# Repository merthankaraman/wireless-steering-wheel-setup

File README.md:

# wireless-steering-wheel-setup
 Wireless steering wheel simulation setup

For 3d model of this project you can check out my friend's page on grabcad: <br>
https://grabcad.com/library/wireless-communication-steering-wheel-project-pedal-part-trial-1

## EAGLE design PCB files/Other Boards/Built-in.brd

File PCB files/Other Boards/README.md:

# arduino-uno-nrf2401
 Arduino board with nrf2401 and screw terminal pinout
 
### Schematic Of the Shield
<br/><br/>

### Board Of the Shield
<br/><br/>

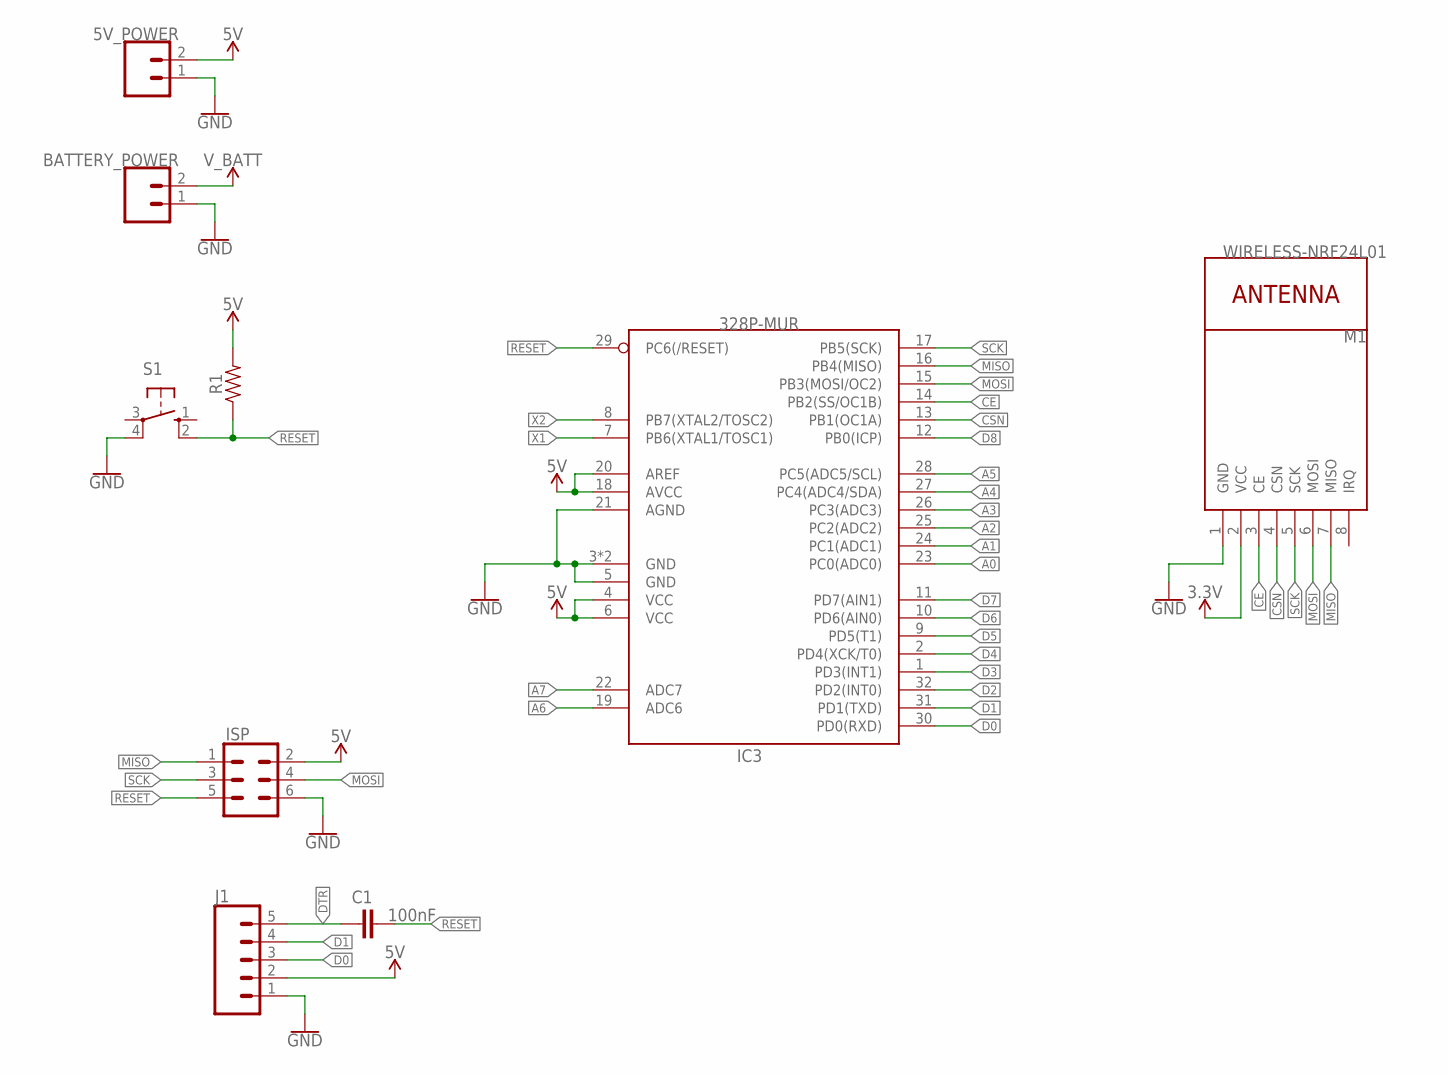
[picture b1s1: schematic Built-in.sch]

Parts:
5V_POWER: CONN_025MM; SCREWTERMINAL-5MM-2
BATTERY_POWER: CONN_025MM; SCREWTERMINAL-5MM-2
C1: 100nF; 0603
IC3: 328P-MUR; VQFN32
ISP: CONN_03X22X3_SILK_MALE_PTH; 2X3
J1: CONN_05; 1X05
M1: WIRELESS-NRF24L01
R1: 0402
S1: 40-XX; B3F-40XX

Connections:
3.3V: M1.2 (VCC)
5V: 5V_POWER.2, IC3.4 (VCC), IC3.6 (VCC), IC3.18 (AVCC), IC3.20 (AREF), ISP.2, J1.2, R1.2
A0: IC3.23 (PC0(ADC0))
A1: IC3.24 (PC1(ADC1))
A2: IC3.25 (PC2(ADC2))
A3: IC3.26 (PC3(ADC3))
A4: IC3.27 (PC4(ADC4/SDA))
A5: IC3.28 (PC5(ADC5/SCL))
A6: IC3.19 (ADC6)
A7: IC3.22 (ADC7)
CE: IC3.14 (PB2(SS/OC1B)), M1.3 (CE)
CSN: IC3.13 (PB1(OC1A)), M1.4 (CSN)
D0: IC3.30 (PD0(RXD)), J1.3
D1: IC3.31 (PD1(TXD)), J1.4
D2: IC3.32 (PD2(INT0))
D3: IC3.1 (PD3(INT1))
D4: IC3.2 (PD4(XCK/T0))
D5: IC3.9 (PD5(T1))
D6: IC3.10 (PD6(AIN0))
D7: IC3.11 (PD7(AIN1))
D8: IC3.12 (PB0(ICP))
DTR: C1.1, J1.5
GND: 5V_POWER.1, BATTERY_POWER.1, IC3.3 (GND), IC3.5 (GND), IC3.21 (AGND), IC3.33 (GND), ISP.6, J1.1, M1.1 (GND), S1.4 (P1)
MISO: IC3.16 (PB4(MISO)), ISP.1, M1.7 (MISO)
MOSI: IC3.15 (PB3(MOSI/OC2)), ISP.4, M1.6 (MOSI)
RESET: C1.2, IC3.29 (PC6(/RESET)), ISP.5, R1.1, S1.2 (S1)
SCK: IC3.17 (PB5(SCK)), ISP.3, M1.5 (SCK)
V_BATT: BATTERY_POWER.2
X1: IC3.7 (PB6(XTAL1/TOSC1))
X2: IC3.8 (PB7(XTAL2/TOSC2))

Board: 2 copper layers, 9 parts (0 on the bottom side), 11 nets, no tracks yet.

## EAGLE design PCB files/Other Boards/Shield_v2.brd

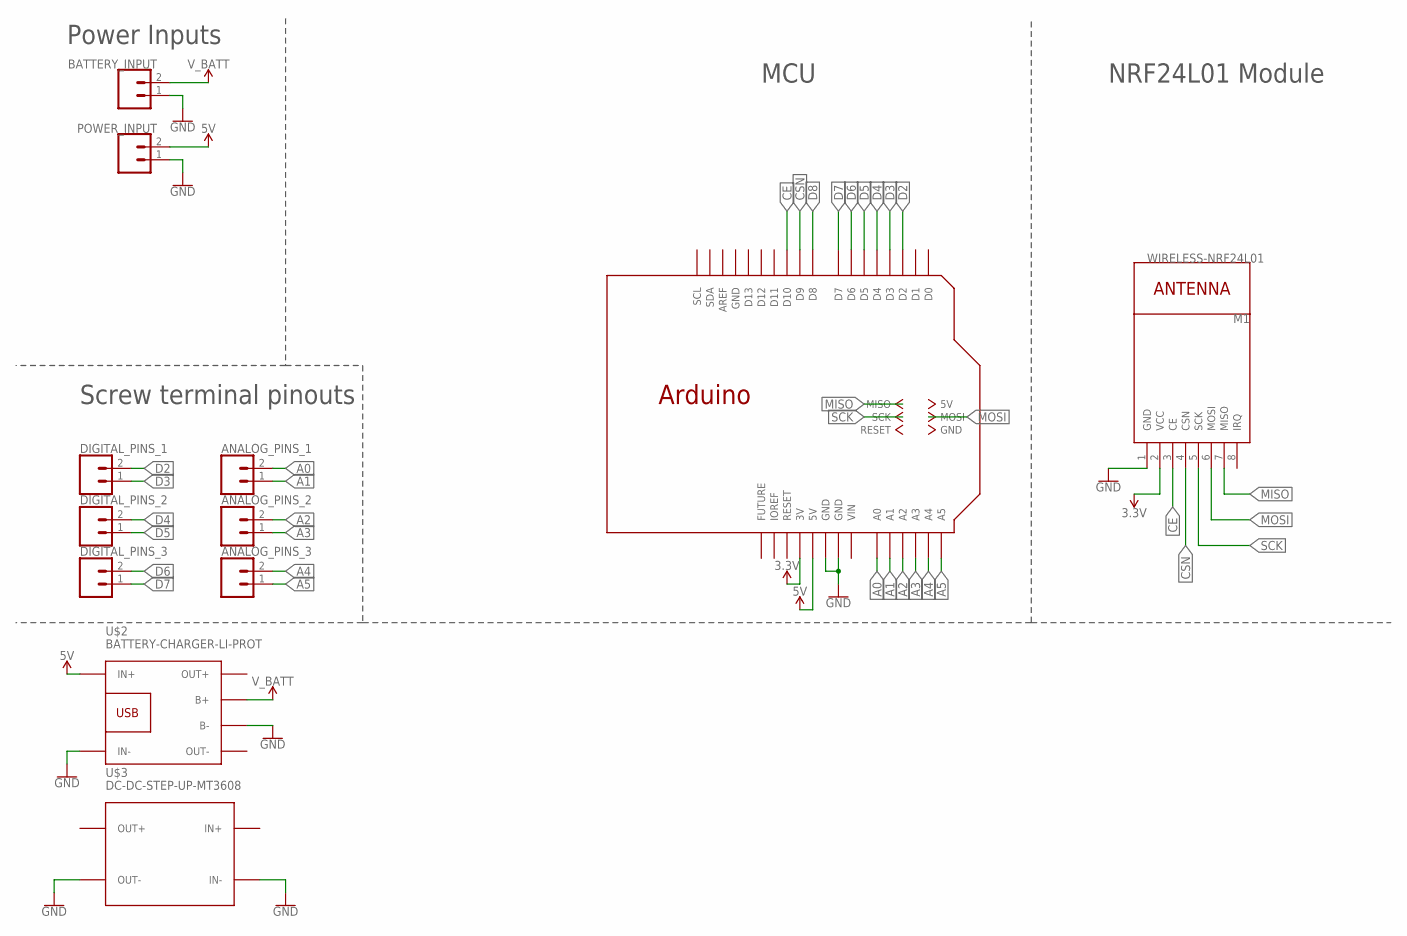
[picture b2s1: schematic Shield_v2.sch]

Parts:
ANALOG_PINS_1, ANALOG_PINS_2, ANALOG_PINS_3: CONN_025MM; SCREWTERMINAL-5MM-2
BATTERY_INPUT: CONN_025MM; SCREWTERMINAL-5MM-2
DIGITAL_PINS_1, DIGITAL_PINS_2, DIGITAL_PINS_3: CONN_025MM; SCREWTERMINAL-5MM-2
M1: WIRELESS-NRF24L01
POWER_INPUT: CONN_025MM; SCREWTERMINAL-5MM-2
U$1: ARDUINO-WITH-ISP
U$2: BATTERY-CHARGER-LI-PROT
U$3: DC-DC-STEP-UP-MT3608

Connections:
3.3V: M1.2 (VCC), U$1.3V
5V: POWER_INPUT.2, U$1.5V, U$2.IN+
A0: ANALOG_PINS_1.2, U$1.A0
A1: ANALOG_PINS_1.1, U$1.A1
A2: ANALOG_PINS_2.2, U$1.A2
A3: ANALOG_PINS_2.1, U$1.A3
A4: ANALOG_PINS_3.2, U$1.A4
A5: ANALOG_PINS_3.1, U$1.A5
CE: M1.3 (CE), U$1.D10
CSN: M1.4 (CSN), U$1.D9
D2: DIGITAL_PINS_1.2, U$1.D2
D3: DIGITAL_PINS_1.1, U$1.D3
D4: DIGITAL_PINS_2.2, U$1.D4
D5: DIGITAL_PINS_2.1, U$1.D5
D6: DIGITAL_PINS_3.2, U$1.D6
D7: DIGITAL_PINS_3.1, U$1.D7
D8: U$1.D8
GND: BATTERY_INPUT.1, M1.1 (GND), POWER_INPUT.1, U$1.GND, U$1.GND$2 (GND), U$1.GND$3 (GND), U$2.B-, U$2.IN-, U$3.IN-, U$3.OUT-
MISO: M1.7 (MISO), U$1.MISO
MOSI: M1.6 (MOSI), U$1.MOSI
SCK: M1.5 (SCK), U$1.SCK
VIN: U$1.VIN
V_BATT: BATTERY_INPUT.2, U$2.B+

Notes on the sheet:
Power Inputs
Screw terminal pinouts
MCU
NRF24L01 Module

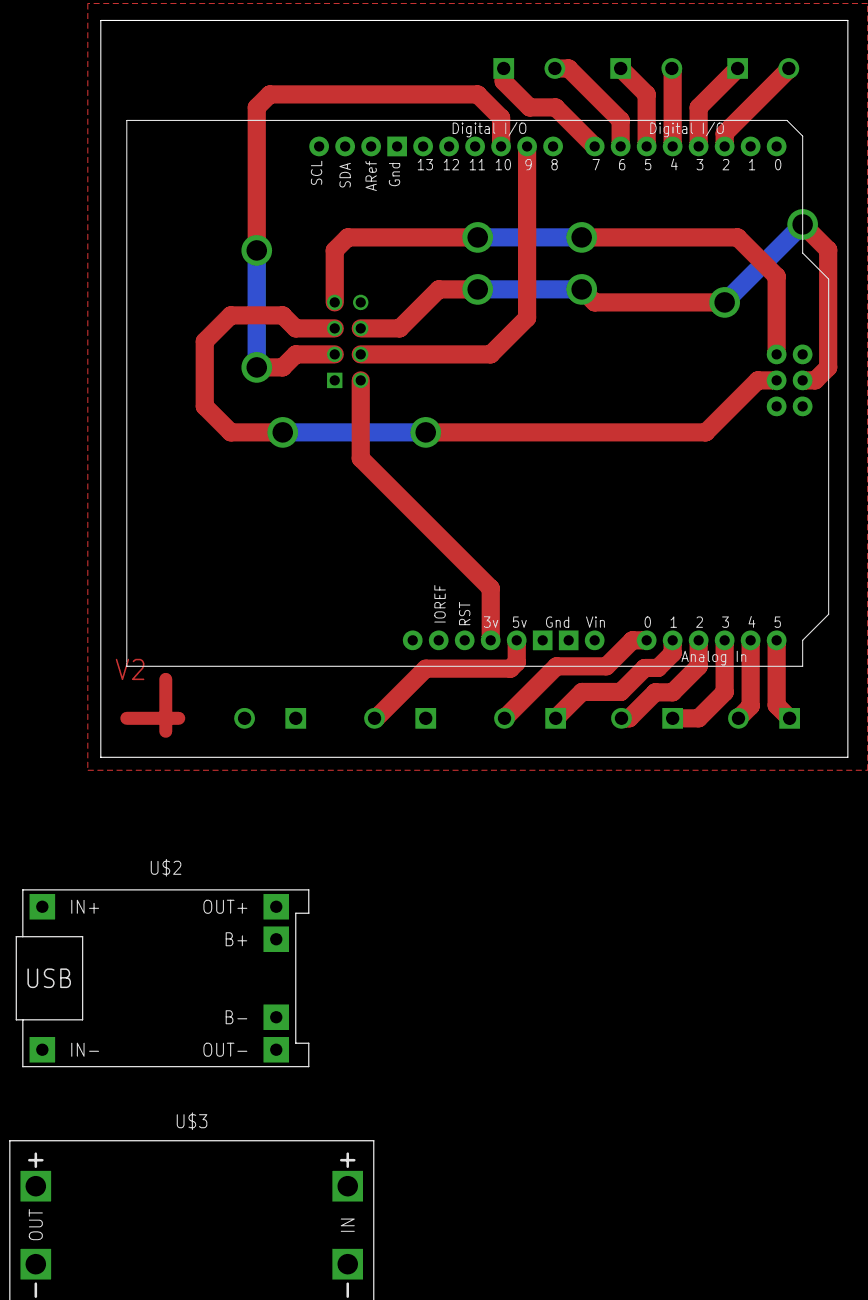
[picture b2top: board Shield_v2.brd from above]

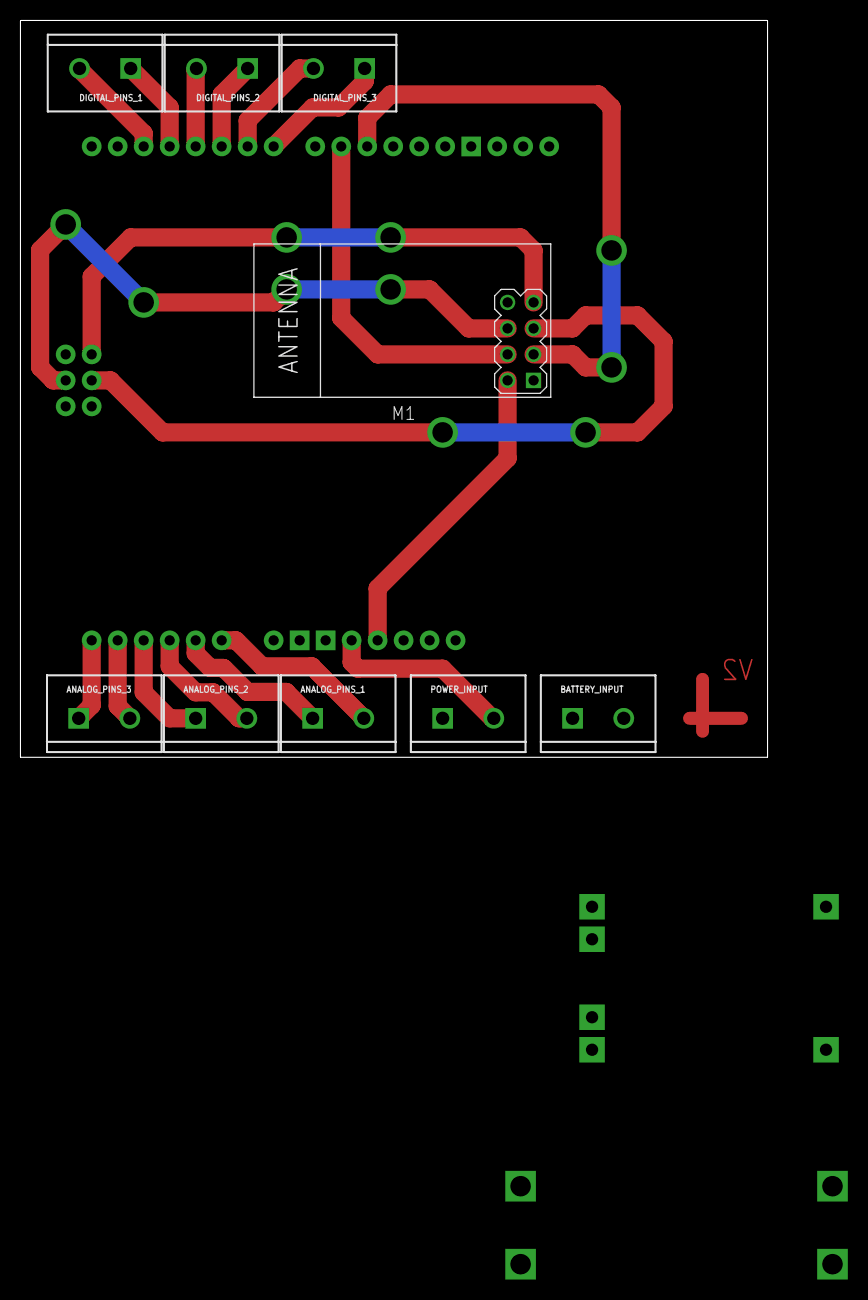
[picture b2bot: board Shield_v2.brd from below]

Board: 2 copper layers, 73.0 x 72.0 mm, 12 parts (9 on the bottom side), 21 nets.

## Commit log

2022-11-29 29.11.22
2023-03-05 Board files improved
2023-03-05 3D parts (pedals) added

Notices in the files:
parts and their libraries:
Arduino-ucs: Copyright (c) 2016-2017 Arduino LLC.  All right reserved.
diy-modules: Released under the Creative Commons Attribution 4.0 International License: http://creativecommons.org/licenses/by/4.0
